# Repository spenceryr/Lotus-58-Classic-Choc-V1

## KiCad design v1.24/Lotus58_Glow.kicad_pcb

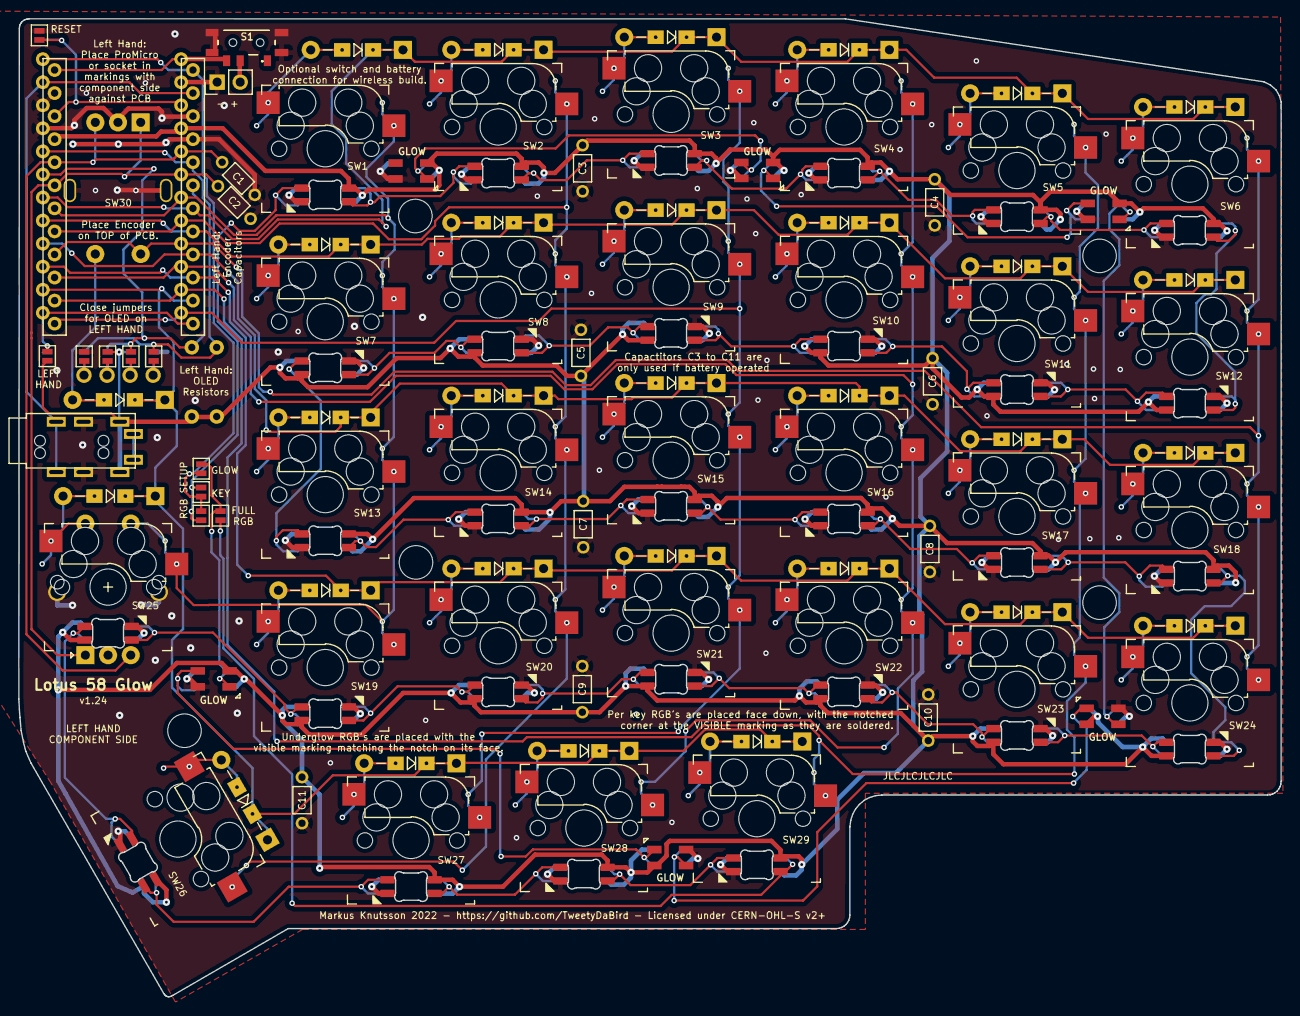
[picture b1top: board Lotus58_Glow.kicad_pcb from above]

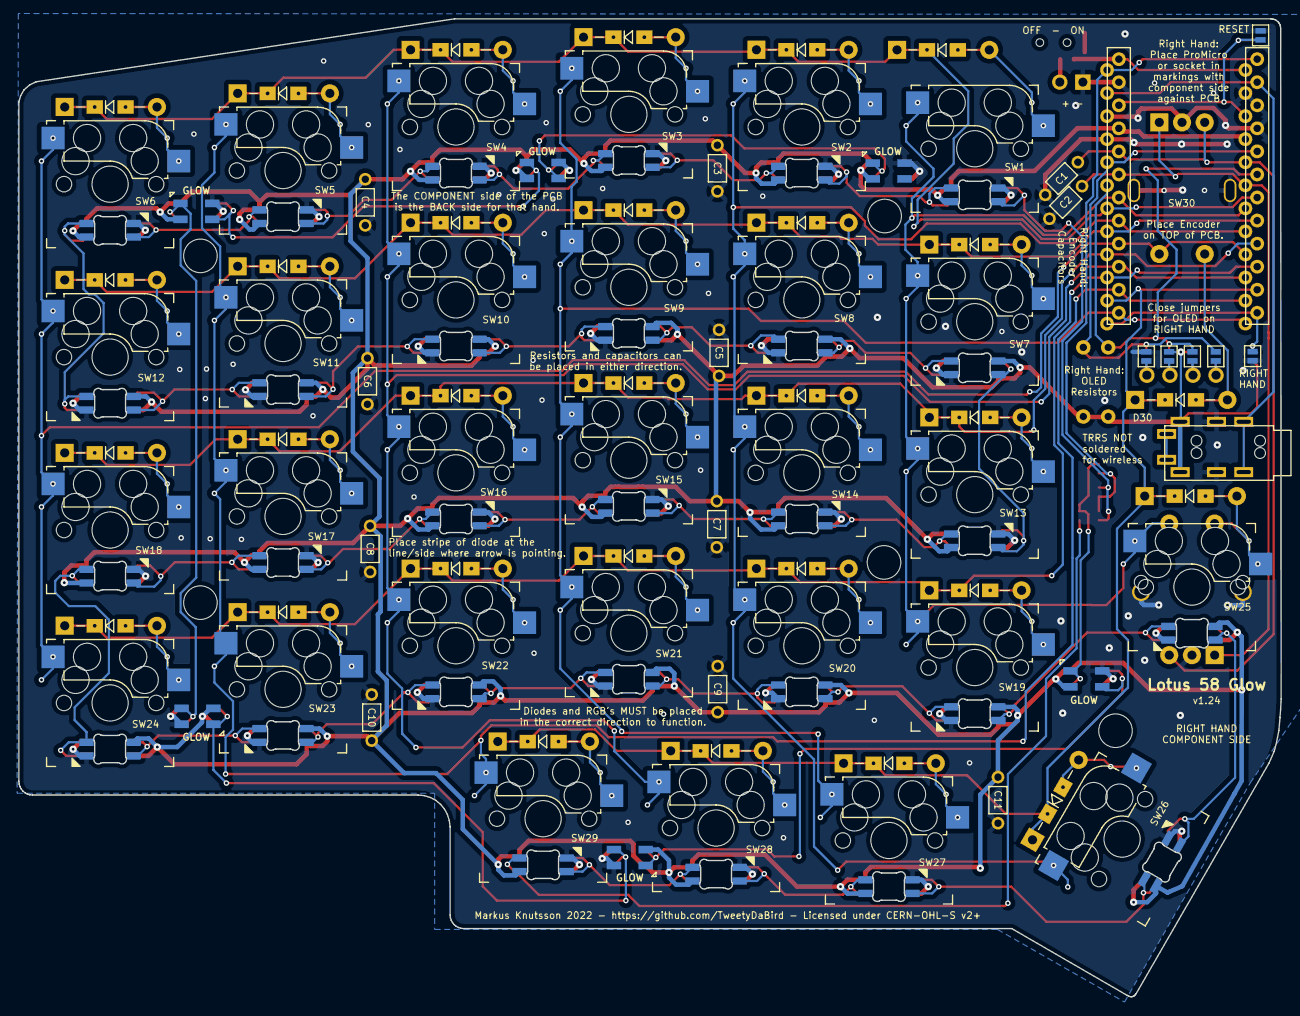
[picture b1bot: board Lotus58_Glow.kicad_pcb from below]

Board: 2 copper layers, 139.1 x 107.7 mm, 135 parts (38 on the bottom side), 93 nets.

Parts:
C1, C2, C3, C4, C5, C6, C7, C8, C9, C10, C11: 100nF; RESISTOR_Reversible
D1, D2, D3, D4, D5, D6, D7, D8, D9, D10, D11, D12, D13, D14, D15, D16, D17, D18, D19, D20, D21, D22, D23, D24, D25, D26, D27, D28, D29, D30: 1N4148/1N4148W; Diode_DO35_SOD123
J1: PJ-320A; MJ-4PP-9_alim
J2: Conn_01x02; PinHeader_1x02_P2.54mm_Vertical
JP1, JP2: RESET; Jumper_Mini
JP3: LEFT; Jumper_Mini
JP4: RIGHT; Jumper_Mini
JP5, JP6, JP7, JP8, JP9, JP10, JP11, JP12: Jumper_NO_Small; Jumper_Mini
JP13, JP14, JP15, JP16: FULL; Jumper_Mini
LED1, LED2, LED3, LED4, LED5, LED6, LED7, LED8, LED9, LED10, LED11, LED12, LED13, LED14, LED15, LED16, LED17, LED18, LED19, LED20, LED21, LED22, LED23, LED24, LED25, LED26, LED27, LED28, LED29: SK6812MINI-E; MX_SK6812MINI-E_REVERSIBLE
LED30, LED31, LED32, LED33, LED34, LED35: SK6812MINI; LED_SK6812MINI_PLCC4_3.5x3.5mm_P1.75mm
P1: OLED; SSD1306-0.91-OLED-4pin-128x32
R1, R2: 4k7; R_Axial_DIN0207_L6.3mm_D2.5mm_P7.62mm_Horizontal
S1: MSK12C02
SW1, SW2, SW3, SW4, SW5, SW6, SW7, SW8, SW9, SW10, SW11, SW12, SW13, SW14, SW15, SW16, SW17, SW18, SW19, SW20, SW21, SW22, SW23, SW24, SW25, SW26, SW27, SW28, SW29: Kailh hotswap MX socket; Kailh_socket_MX_reversible_RGB
SW30: Rotary_Encoder_Switch; RotaryEncoder_Alps_EC11E-Switch_Vertical_H20_special
SW31: Rotary_Encoder_Switch; RotaryEncoder_Alps_EC11E-Switch_Special
TH1, TH2, TH3, TH4, TH5: HOLE; MountingHole_3.7mm
U1: ProMicro; ProMicro_Reversible

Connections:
/Batt: J2.2, S1.B1 (COM)
A: C2.2, SW30.A, SW31.A, U1.19 (A2/PF5)
Alt: D25.2 (A), SW25.2, SW31.S2
B: C1.1, SW30.B, SW31.B, U1.20 (A3/PF4)
Battery: S1.C1 (NO), U1.24 (RAW)
DATA: J1.R2, U1.2 (RX1/PD2)
GND: C1.2, C2.1, C3.2, C4.2, C5.2, C6.2, C7.2, C8.2, C9.2, C10.2, C11.2, J1.R1, J2.1, JP1.2, JP2.2, JP4.2, JP5.2, JP12.2, LED1.3 (GND), LED2.3 (GND), LED3.3 (GND), LED4.3 (GND), LED5.3 (GND), LED6.3 (GND), LED7.3 (GND), LED8.3 (GND), LED9.3 (GND), LED10.3 (GND), LED11.3 (GND), LED12.3 (GND), LED13.3 (GND), LED14.3 (GND), LED15.3 (GND), LED16.3 (GND), LED17.3 (GND), LED18.3 (GND), LED19.3 (GND), LED20.3 (GND), LED21.3 (GND), LED22.3 (GND), LED23.3 (GND), LED24.3 (GND), LED25.3 (GND), LED26.3 (GND), LED27.3 (GND), LED28.3 (GND), LED29.3 (GND), LED30.2 (VSS), LED31.2 (VSS), LED32.2 (VSS), LED33.2 (VSS), LED34.2 (VSS), LED35.2 (VSS), S1.MP, SW30.C, SW30.MP1 (GND), SW30.MP2 (GND), SW31.C, SW31.MP1 (GND), SW31.MP2 (GND), U1.3 (GND), U1.4 (GND), U1.23 (GND)
Hand: JP3.1, JP4.1, U1.12 (9/PB5)
LED: JP13.1, JP14.1, JP16.1, U1.1 (TX0/PD3)
unnamed: D1.2 (A), SW1.2
unnamed: D2.2 (A), SW2.2
unnamed: D3.2 (A), SW3.2
unnamed: D4.2 (A), SW4.2
unnamed: D5.2 (A), SW5.2
unnamed: D6.2 (A), SW6.2
unnamed: D7.2 (A), SW7.2
unnamed: D8.2 (A), SW8.2
unnamed: D9.2 (A), SW9.2
unnamed: D10.2 (A), SW10.2
unnamed: D11.2 (A), SW11.2
unnamed: D12.2 (A), SW12.2
unnamed: D13.2 (A), SW13.2
unnamed: D14.2 (A), SW14.2
unnamed: D15.2 (A), SW15.2
unnamed: D16.2 (A), SW16.2
unnamed: D17.2 (A), SW17.2
unnamed: D18.2 (A), SW18.2
unnamed: D19.2 (A), SW19.2
unnamed: D20.2 (A), SW20.2
unnamed: D21.2 (A), SW21.2
unnamed: D22.2 (A), SW22.2
unnamed: D23.2 (A), SW23.2
unnamed: D24.2 (A), SW24.2
unnamed: D26.2 (A), SW26.2
unnamed: D27.2 (A), SW27.2
unnamed: D28.2 (A), SW28.2
unnamed: D29.2 (A), SW29.2
unnamed: D30.2 (A), SW30.S1
unnamed: JP5.1, JP9.1, P1.1
unnamed: JP6.1, JP10.1, P1.2
unnamed: JP7.1, JP11.1, P1.3
unnamed: JP8.1, JP12.1, P1.4
unnamed: LED1.2 (DOUT), LED2.4 (DIN)
unnamed: LED2.2 (DOUT), LED3.4 (DIN)
unnamed: LED3.2 (DOUT), LED4.4 (DIN)
unnamed: LED4.2 (DOUT), LED5.4 (DIN)
unnamed: LED5.2 (DOUT), LED6.4 (DIN)
unnamed: LED7.4 (DIN), LED8.2 (DOUT)
unnamed: LED8.4 (DIN), LED9.2 (DOUT)
unnamed: LED9.4 (DIN), LED10.2 (DOUT)
unnamed: LED10.4 (DIN), LED11.2 (DOUT)
unnamed: LED11.4 (DIN), LED12.2 (DOUT)
unnamed: LED6.2 (DOUT), LED12.4 (DIN)
unnamed: LED13.2 (DOUT), LED14.4 (DIN)
unnamed: LED7.2 (DOUT), LED13.4 (DIN)
unnamed: LED14.2 (DOUT), LED15.4 (DIN)
unnamed: LED15.2 (DOUT), LED16.4 (DIN)
unnamed: LED16.2 (DOUT), LED17.4 (DIN)
unnamed: LED17.2 (DOUT), LED18.4 (DIN)
unnamed: LED18.2 (DOUT), LED24.4 (DIN)
unnamed: LED19.2 (DOUT), LED25.4 (DIN)
unnamed: LED19.4 (DIN), LED20.2 (DOUT)
unnamed: LED20.4 (DIN), LED21.2 (DOUT)
unnamed: LED21.4 (DIN), LED22.2 (DOUT)
unnamed: LED22.4 (DIN), LED23.2 (DOUT)
unnamed: LED23.4 (DIN), LED24.2 (DOUT)
unnamed: LED25.2 (DOUT), LED26.4 (DIN)
unnamed: LED26.2 (DOUT), LED27.4 (DIN)
unnamed: LED27.2 (DOUT), LED28.4 (DIN)
unnamed: LED28.2 (DOUT), LED29.4 (DIN)
unnamed: LED30.1 (DOUT), LED31.3 (DIN)
unnamed: LED31.1 (DOUT), LED32.3 (DIN)
unnamed: LED32.1 (DOUT), LED33.3 (DIN)
unnamed: LED33.1 (DOUT), LED34.3 (DIN)
unnamed: LED34.1 (DOUT), LED35.3 (DIN)
RESET: JP1.1, JP2.1, U1.22 (RST)
RGB_GLOW: JP13.2, JP15.2, LED30.3 (DIN)
RGB_KEY: JP14.2, JP16.2, LED1.4 (DIN)
RGB_LINK: JP15.1, LED29.2 (DOUT)
SCL: JP7.2, JP10.2, R1.2, U1.6 (3/PD0)
SDA: JP8.2, JP9.2, R2.2, U1.5 (2/PD1)
VCC: C3.1, C4.1, C5.1, C6.1, C7.1, C8.1, C9.1, C10.1, C11.1, J1.T, JP3.2, JP6.2, JP11.2, LED1.1 (VCC), LED2.1 (VCC), LED3.1 (VCC), LED4.1 (VCC), LED5.1 (VCC), LED6.1 (VCC), LED7.1 (VCC), LED8.1 (VCC), LED9.1 (VCC), LED10.1 (VCC), LED11.1 (VCC), LED12.1 (VCC), LED13.1 (VCC), LED14.1 (VCC), LED15.1 (VCC), LED16.1 (VCC), LED17.1 (VCC), LED18.1 (VCC), LED19.1 (VCC), LED20.1 (VCC), LED21.1 (VCC), LED22.1 (VCC), LED23.1 (VCC), LED24.1 (VCC), LED25.1 (VCC), LED26.1 (VCC), LED27.1 (VCC), LED28.1 (VCC), LED29.1 (VCC), LED30.4 (VDD), LED31.4 (VDD), LED32.4 (VDD), LED33.4 (VDD), LED34.4 (VDD), LED35.4 (VDD), R1.1, R2.1, U1.21 (VCC)
col0: SW6.1, SW12.1, SW18.1, SW24.1, SW30.S2, U1.16 (15/PB1)
col1: SW5.1, SW11.1, SW17.1, SW23.1, SW29.1, U1.14 (16/PB2)
col2: SW4.1, SW10.1, SW16.1, SW22.1, SW28.1, U1.15 (14/PB3)
col3: SW3.1, SW9.1, SW15.1, SW21.1, SW27.1, U1.13 (10/PB6)
col4: SW2.1, SW8.1, SW14.1, SW20.1, SW26.1, U1.17 (A0/PF7)
col5: SW1.1, SW7.1, SW13.1, SW19.1, SW25.1, SW31.S1, U1.18 (A1/PF6)
row0: D1.1 (K), D2.1 (K), D3.1 (K), D4.1 (K), D5.1 (K), D6.1 (K), U1.7 (4/PD4)
row1: D7.1 (K), D8.1 (K), D9.1 (K), D10.1 (K), D11.1 (K), D12.1 (K), U1.8 (5/PC6)
row2: D13.1 (K), D14.1 (K), D15.1 (K), D16.1 (K), D17.1 (K), D18.1 (K), U1.9 (6/PD7)
row3: D19.1 (K), D20.1 (K), D21.1 (K), D22.1 (K), D23.1 (K), D24.1 (K), U1.10 (7/PE6)
row4: D25.1 (K), D26.1 (K), D27.1 (K), D28.1 (K), D29.1 (K), D30.1 (K), U1.11 (8/PB4)

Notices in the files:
v1.24/Lotus58_Glow.kicad_pcb:
Licensed under CERN-OHL-S v2 or any superseding version
Markus Knutsson 2022 - https://github.com/TweetyDaBird - Licensed under CERN-OHL-S v2+
